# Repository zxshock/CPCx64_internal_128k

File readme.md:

Requires a second bank to be piggybacked on top of the existing DRAMs. Various signals have to be taken from various chips on the board. Names according to the original schematic by Amstrad.
This has been tested on a german CPC464 with DD-1 and 6128 ROM. I see no reason why it shouldn't work on a 664 either - but this is untested from my side.

Credits: 
CPC6128.JED by Amstrad, reverse engineered by gerald, initial version by Porchy.
Schematic by Amstrad
PCB Layout by shock__

License (PCB): CC-BY-SA-NC (https://creativecommons.org/licenses/by-nc-sa/2.0/) - NC/non-commercial means 'no considerable profit' in my understanding, you're of course free to sell boards/parts for the price you paid and take a reasonable fee if you offer pre-assembled ones.

Developed and tested on a Schneider CPC464 in 10/2017

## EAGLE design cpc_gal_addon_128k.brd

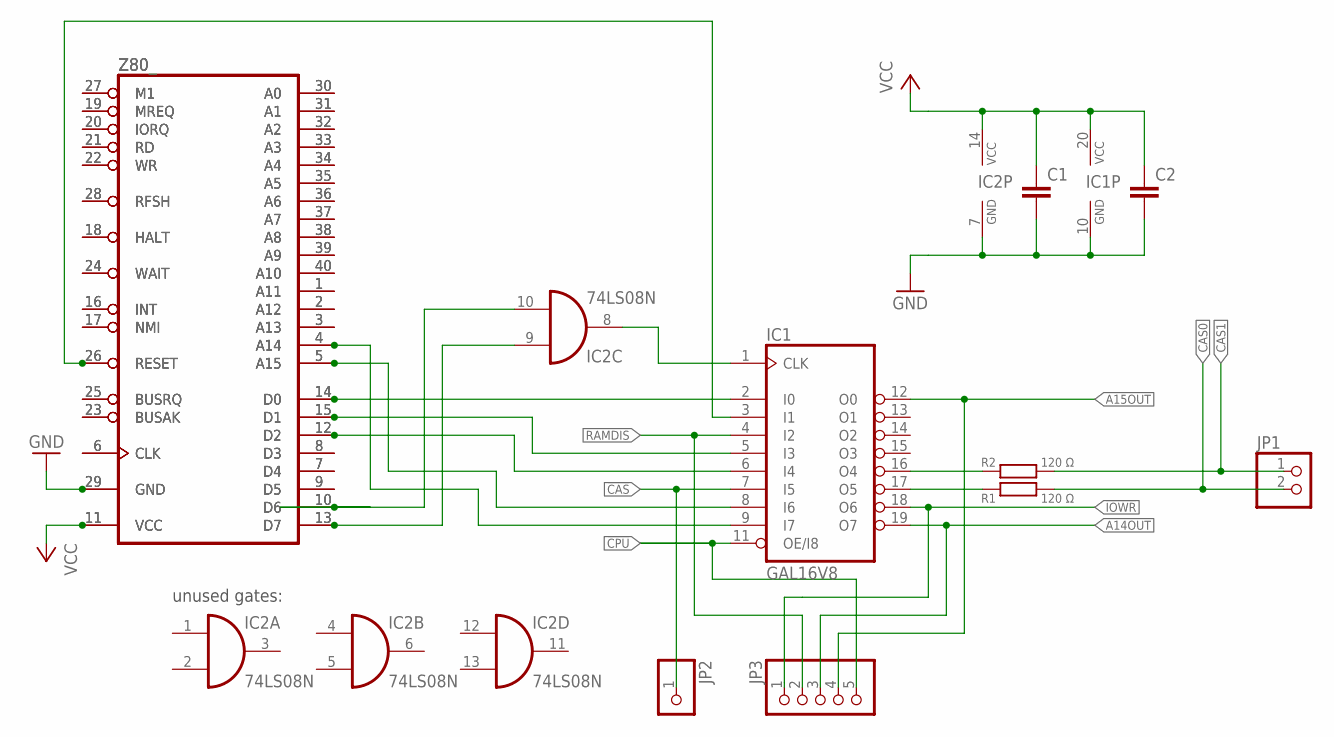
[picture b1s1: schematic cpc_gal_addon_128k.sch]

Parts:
C1, C2: C-EU025-025X050; C025-025X050
IC1: GAL16V8; DIL20
IC2: 74LS08N; DIL14
JP1: PINHD-1X2; 1X02
JP2: PINHD-1X1; 1X01
JP3: PINHD-1X5; 1X05
R1, R2: 120 Ω; 0204/5
Z80, Z80_: Z80CPU; DIL40

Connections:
!CAS: IC1.7 (I5), JP2.1
!CPU: IC1.11 (OE/I8), JP3.5
!IOWR: IC1.18 (O6), JP3.1
A14OUT: IC1.19 (O7), JP3.3
A15OUT: IC1.12 (O0), JP3.4
CAS0: JP1.2, R1.2
CAS1: JP1.1, R2.2
GND: C1.2, C2.2, IC1.10 (GND), IC2.7 (GND), Z80.29 (GND), Z80_.29 (GND)
unnamed: IC2.9 (I0), Z80.13 (D7), Z80_.13 (D7)
unnamed: IC2.10 (I1), Z80.10 (D6), Z80_.10 (D6)
unnamed: IC1.1 (CLK), IC2.8 (O)
unnamed: IC1.2 (I0), Z80.14 (D0), Z80_.14 (D0)
unnamed: IC1.3 (I1), Z80.26 (RESET), Z80_.26 (RESET)
unnamed: IC1.5 (I3), Z80.15 (D1), Z80_.15 (D1)
unnamed: IC1.6 (I4), Z80.12 (D2), Z80_.12 (D2)
unnamed: IC1.8 (I6), Z80.5 (A15), Z80_.5 (A15)
unnamed: IC1.9 (I7), Z80.4 (A14), Z80_.4 (A14)
unnamed: IC1.17 (O5), R1.1
unnamed: IC1.16 (O4), R2.1
unnamed: Z80.30 (A0), Z80_.30 (A0)
unnamed: Z80.31 (A1), Z80_.31 (A1)
unnamed: Z80.32 (A2), Z80_.32 (A2)
unnamed: Z80.33 (A3), Z80_.33 (A3)
unnamed: Z80.34 (A4), Z80_.34 (A4)
unnamed: Z80.35 (A5), Z80_.35 (A5)
unnamed: Z80.36 (A6), Z80_.36 (A6)
unnamed: Z80.37 (A7), Z80_.37 (A7)
unnamed: Z80.38 (A8), Z80_.38 (A8)
unnamed: Z80.39 (A9), Z80_.39 (A9)
unnamed: Z80.40 (A10), Z80_.40 (A10)
unnamed: Z80.1 (A11), Z80_.1 (A11)
unnamed: Z80.2 (A12), Z80_.2 (A12)
unnamed: Z80.3 (A13), Z80_.3 (A13)
unnamed: Z80.8 (D3), Z80_.8 (D3)
unnamed: Z80.7 (D4), Z80_.7 (D4)
unnamed: Z80.9 (D5), Z80_.9 (D5)
unnamed: Z80.27 (M1), Z80_.27 (M1)
unnamed: Z80.19 (MREQ), Z80_.19 (MREQ)
unnamed: Z80.20 (IORQ), Z80_.20 (IORQ)
unnamed: Z80.21 (RD), Z80_.21 (RD)
unnamed: Z80.22 (WR), Z80_.22 (WR)
unnamed: Z80.28 (RFSH), Z80_.28 (RFSH)
unnamed: Z80.18 (HALT), Z80_.18 (HALT)
unnamed: Z80.24 (WAIT), Z80_.24 (WAIT)
unnamed: Z80.16 (INT), Z80_.16 (INT)
unnamed: Z80.17 (NMI), Z80_.17 (NMI)
unnamed: Z80.25 (BUSRQ), Z80_.25 (BUSRQ)
unnamed: Z80.23 (BUSAK), Z80_.23 (BUSAK)
unnamed: Z80.6 (CLK), Z80_.6 (CLK)
RAMDIS: IC1.4 (I2), JP3.2
VCC: C1.1, C2.1, IC1.20 (VCC), IC2.14 (VCC), Z80.11 (VCC), Z80_.11 (VCC)

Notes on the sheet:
unused gates:

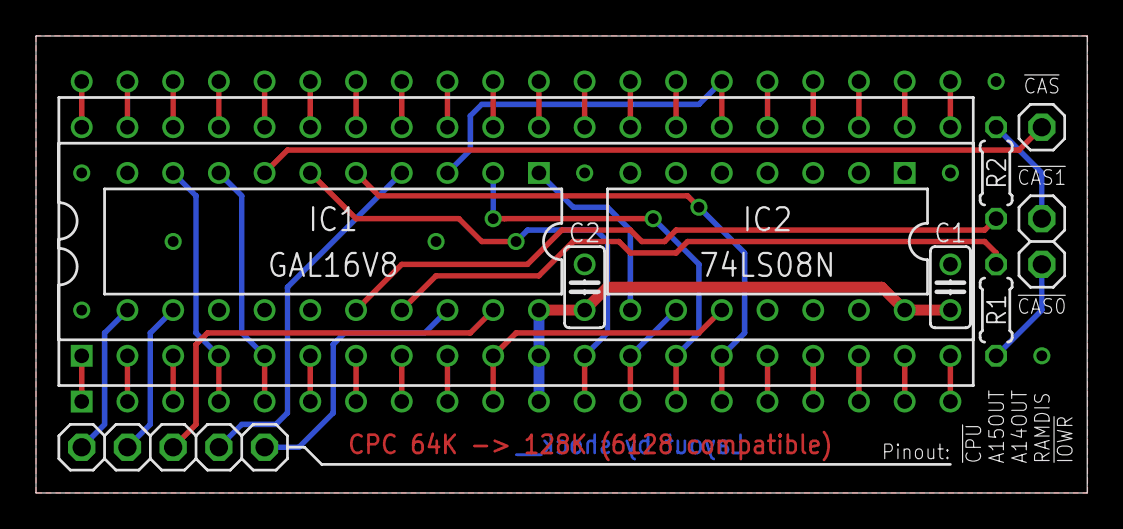
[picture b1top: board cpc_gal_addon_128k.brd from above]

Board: 2 copper layers, 58.4 x 25.4 mm, 11 parts (0 on the bottom side), 51 nets.
